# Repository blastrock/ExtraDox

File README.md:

# ExtraDox (v2)

The ExtraDox is a split keyboard based off the ErgoDox. The main difference is
that it has an additional row of keys on the top. Also, it is a low-profile
keyboard designed for Choc v1 switches.

It features:

- An additional row of keys over the ErgoDox
- An USB-C port
- A single-board design (actually two boards), no extra controller board
- A TRRS connection between the two sides
- The 3 usual status LED
- The case is only 8mm thick, the keys are 18mm high from the desk

## What you need to build this keyboard

- The PCBs and their components (the MCU is soldered on the main board)
- The 3D-printed case
- 14x M2.5x8 screws and nuts
- 10x rubber pads to put under the keyboard to prevent slipping
- 90x Kailh Choc Hotswap sockets
- 90x Kailh Choc switches
- 82x 1u key caps
- 4x 1.5u key caps
- 4x 2u key caps
- 3x SMD status LED (see the Kicad project for details)
- 2x TRRS connector (see the Kicad project for details)
- 1x TRRS cable
- 1x USB-c cable

## About this keyboard

### PCB

The PCB is designed in Kicad. It is a SMD design and the project includes
component references from JLCPCB.

### Case

The case is designed to be 3D-printed. The case is screwed together with 7
M2.5x8 screws on each side, and their corresponding bolts.

### Firmware

[Here](https://github.com/blastrock/qmk_firmware/tree/extradox/keyboards/extradox) is a a fork of the QMK firmware with support for the ExtraDox.

## Known issues

Some capacitors are located right under an hotswap socket. It is still possible
to solder it, but the socket gets a little tilted.

## License

This work is licensed under a [Creative Commons Attribution-NonCommercial-ShareAlike 4.0 International License](http://creativecommons.org/licenses/by-nc-sa/4.0/).

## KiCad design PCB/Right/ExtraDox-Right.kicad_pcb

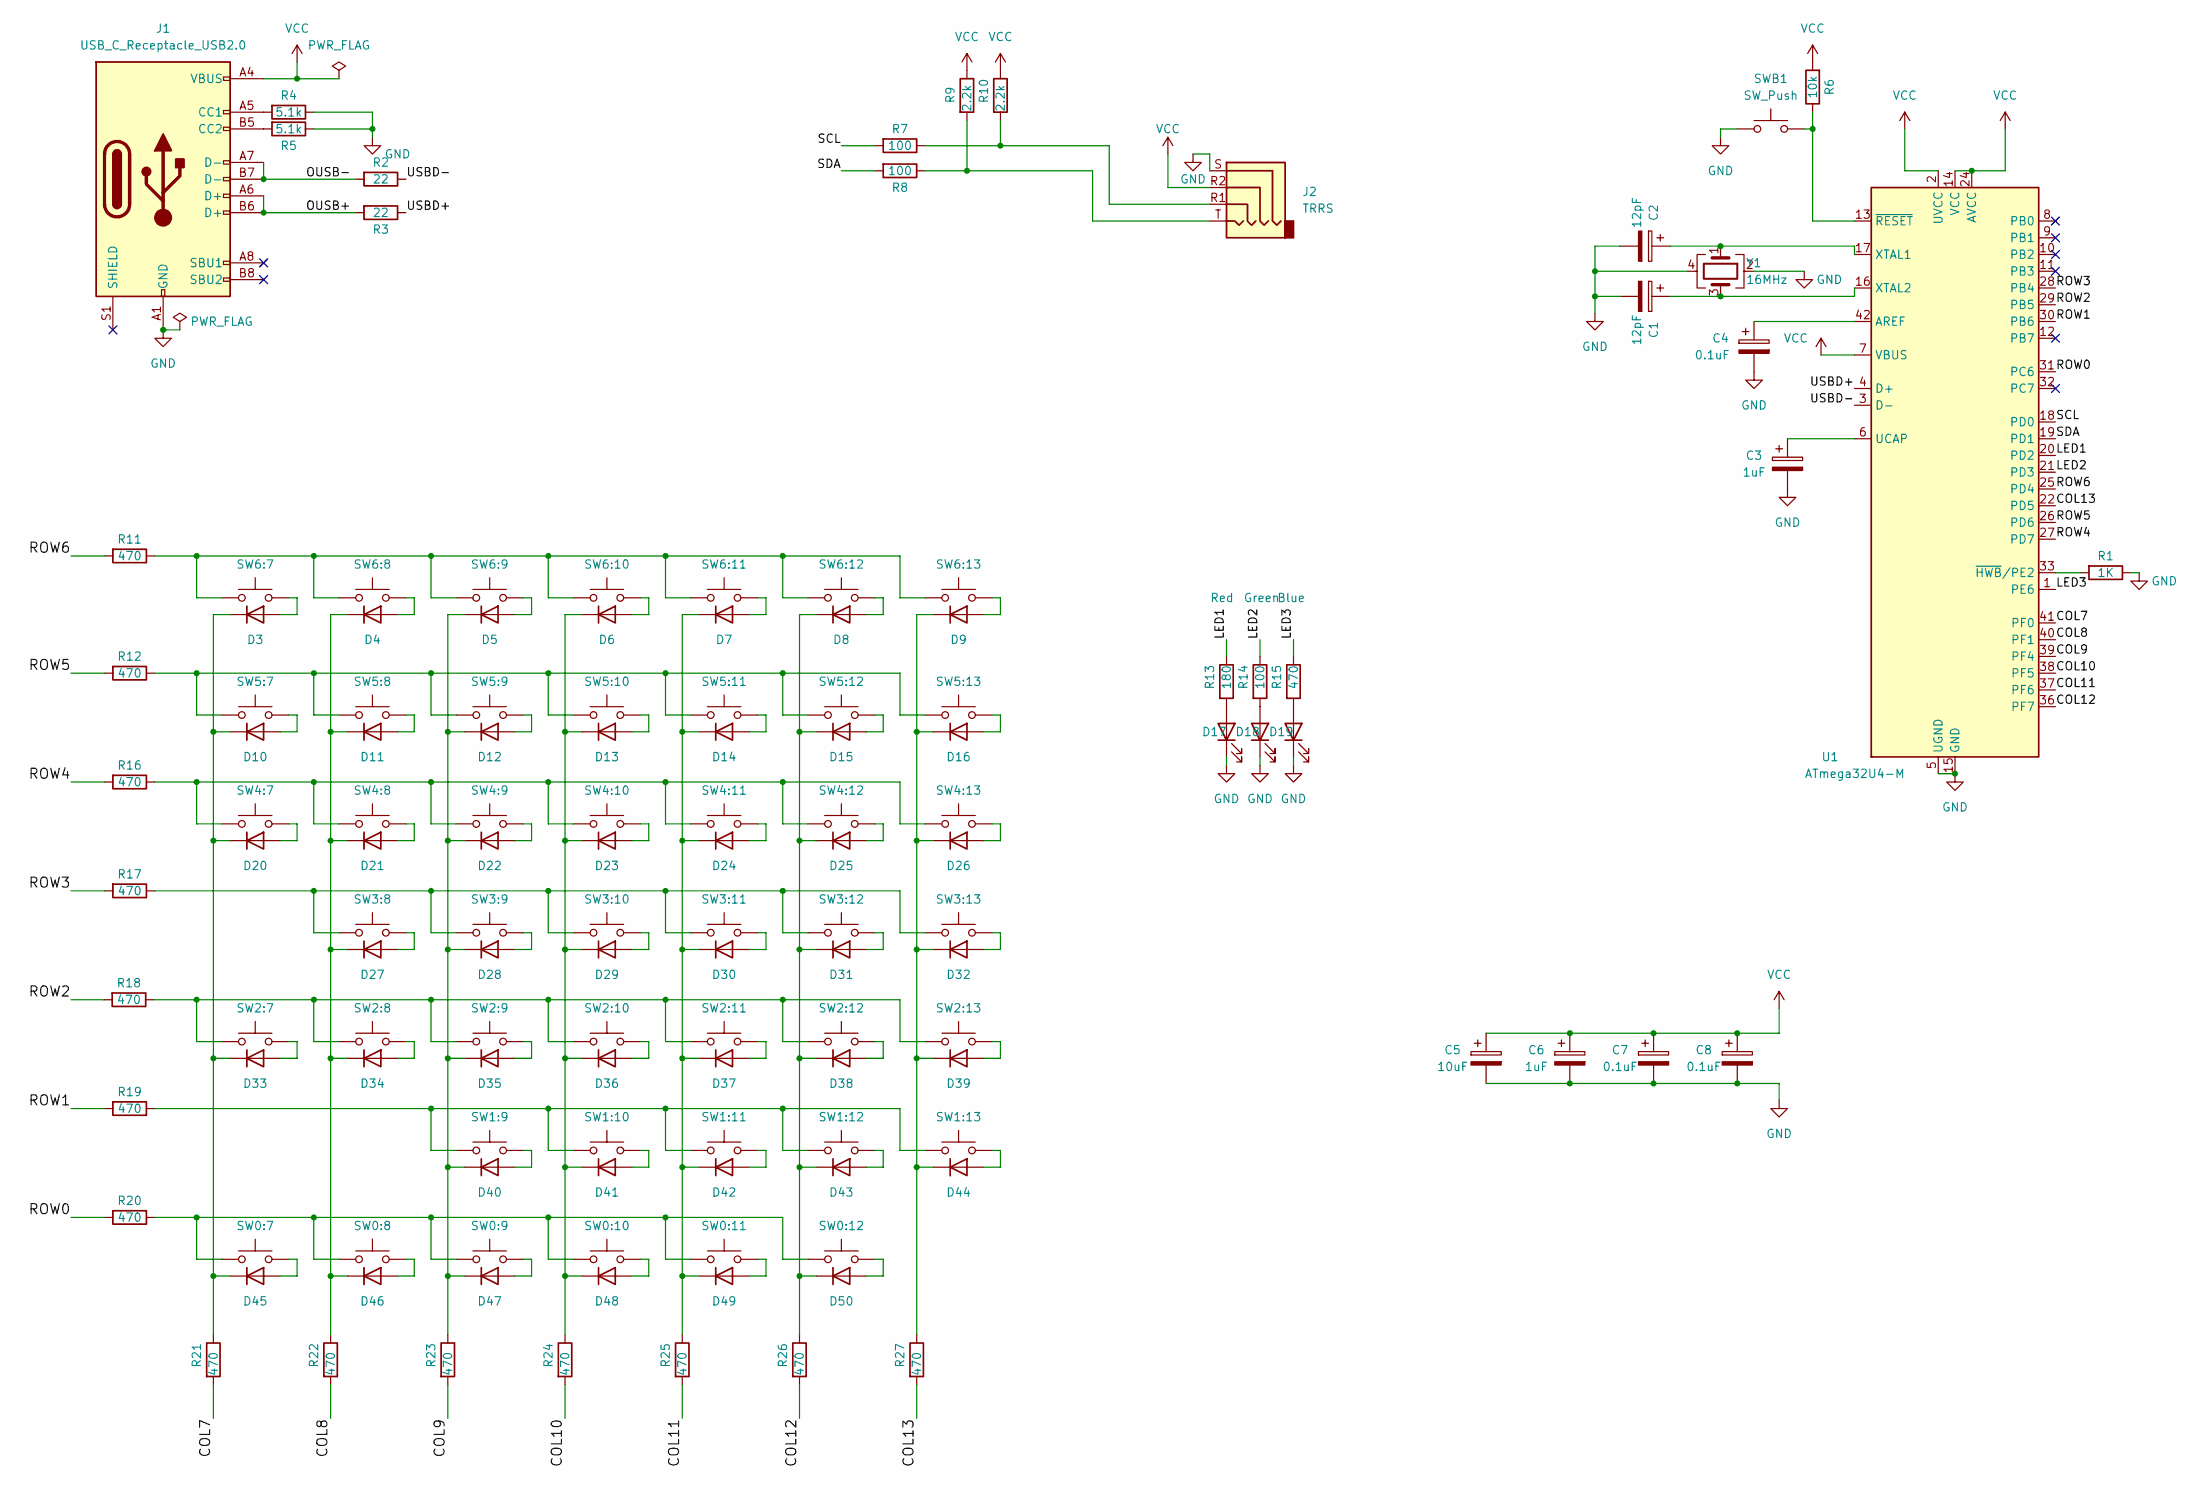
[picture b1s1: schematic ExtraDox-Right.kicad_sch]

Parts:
C1, C2: 12pF; C_0402_1005Metric; LCSC C1547
C3, C6: 1uF; C_0402_1005Metric; LCSC C52923
C4, C7, C8: 0.1uF; C_0402_1005Metric; LCSC C307331
C5: 10uF; C_0402_1005Metric; LCSC C15525
D3, D4, D5, D6, D7, D8, D9, D10, D11, D12, D13, D14, D15, D16, D20, D21, D22, D23, D24, D25, D26, D27, D28, D29, D30, D31, D32, D33, D34, D35, D36, D37, D38, D39, D40, D41, D42, D43, D44, D45, D46, D47, D48, D49, D50: D; D_SOD-123F; LCSC C64898
D17: Red; D_0603_1608Metric; LCSC C2286
D18: Green; D_0603_1608Metric; LCSC C72043
D19: Blue; D_0603_1608Metric; LCSC C72041
J1: USB_C_Receptacle_USB2.0; HRS_CX90M-16P; LCSC C2889324
J2: TRRS; TRRS-PJ-320A
R1: 1K; R_0402_1005Metric; LCSC C11702
R2, R3: 22; R_0402_1005Metric; LCSC C25092
R4, R5: 5.1k; R_0402_1005Metric; LCSC C25905
R6: 10k; R_0402_1005Metric; LCSC C25744
R7, R8, R14: 100; R_0402_1005Metric; LCSC C25076
R9, R10: 2.2k; R_0402_1005Metric; LCSC C25879
R11, R12, R15, R16, R17, R18, R19, R20, R21, R22, R23, R24, R25, R26, R27: 470; R_0402_1005Metric; LCSC C25117
R13: 180; R_0402_1005Metric; LCSC C25082
SW0:7, SW0:8, SW0:9, SW0:12, SW1:9, SW1:10, SW1:11, SW1:12, SW1:13, SW2:8, SW2:9, SW2:10, SW2:11, SW2:12, SW2:13, SW3:8, SW3:9, SW3:10, SW3:11, SW3:12, SW3:13, SW4:8, SW4:9, SW4:10, SW4:11, SW4:12, SW4:13, SW5:7, SW5:8, SW5:9, SW5:10, SW5:11, SW5:12, SW5:13, SW6:7, SW6:8, SW6:9, SW6:10, SW6:11, SW6:12, SW6:13: SW_Push; KailhHotswapChoc1
SW0:10, SW0:11: SW_Push; KailhHotswapChoc2
SW2:7, SW4:7: SW_Push; KailhHotswapChoc15
SWB1: SW_Push; TS-1087S; LCSC C455263
U1: ATmega32U4-M; QFN-44-1EP_7x7mm_P0.5mm_EP5.2x5.2mm_ThermalVias_JLCPCB; LCSC C112161
Y1: 16MHz; Crystal_SMD_3225-4Pin_3.2x2.5mm; LCSC C13738

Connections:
/COL7: R21.2, U1.41 (PF0)
/COL8: R22.2, U1.40 (PF1)
/COL9: R23.2, U1.39 (PF4)
/COL10: R24.2, U1.38 (PF5)
/COL11: R25.2, U1.37 (PF6)
/COL12: R26.2, U1.36 (PF7)
/COL13: R27.2, U1.22 (PD5)
/LED1: R13.1, U1.20 (PD2)
/LED2: R14.1, U1.21 (PD3)
/LED3: R15.1, U1.1 (PE6)
/OUSB+: J1.A6 (D+), J1.B6 (D+), R3.2
/OUSB-: J1.A7 (D-), J1.B7 (D-), R2.2
/ROW0: R20.2, U1.31 (PC6)
/ROW1: R19.2, U1.30 (PB6)
/ROW2: R18.2, U1.29 (PB5)
/ROW3: R17.2, U1.28 (PB4)
/ROW4: R16.2, U1.27 (PD7)
/ROW5: R12.2, U1.26 (PD6)
/ROW6: R11.2, U1.25 (PD4)
/SCL: R7.2, U1.18 (PD0)
/SDA: R8.2, U1.19 (PD1)
/USBD+: R3.1, U1.4 (D+)
/USBD-: R2.1, U1.3 (D-)
GND: C1.2, C2.2, C3.2, C4.2, C5.2, C6.2, C7.2, C8.2, D17.1 (K), D18.1 (K), D19.1 (K), J1.A1 (GND), J1.A12 (GND), J1.B1 (GND), J1.B12 (GND), J2.S, R1.1, R4.1, R5.1, SWB1.1, U1.5 (UGND), U1.15 (GND), U1.23 (GND), U1.35 (GND), U1.43 (GND), U1.45 (GND), Y1.2, Y1.4
unnamed: C1.1, U1.16 (XTAL2), Y1.3
unnamed: C2.1, U1.17 (XTAL1), Y1.1
unnamed: C3.1, U1.6 (UCAP)
unnamed: C4.1, U1.42 (AREF)
unnamed: D3.2 (A), SW6:7.2
unnamed: D4.2 (A), SW6:8.2
unnamed: D5.2 (A), SW6:9.2
unnamed: D6.2 (A), SW6:10.2
unnamed: D7.2 (A), SW6:11.2
unnamed: D8.2 (A), SW6:12.2
unnamed: D9.2 (A), SW6:13.2
unnamed: D3.1 (K), D10.1 (K), D20.1 (K), D33.1 (K), D45.1 (K), R21.1
unnamed: D10.2 (A), SW5:7.2
unnamed: D4.1 (K), D11.1 (K), D21.1 (K), D27.1 (K), D34.1 (K), D46.1 (K), R22.1
unnamed: D11.2 (A), SW5:8.2
unnamed: D5.1 (K), D12.1 (K), D22.1 (K), D28.1 (K), D35.1 (K), D40.1 (K), D47.1 (K), R23.1
unnamed: D12.2 (A), SW5:9.2
unnamed: D6.1 (K), D13.1 (K), D23.1 (K), D29.1 (K), D36.1 (K), D41.1 (K), D48.1 (K), R24.1
unnamed: D13.2 (A), SW5:10.2
unnamed: D7.1 (K), D14.1 (K), D24.1 (K), D30.1 (K), D37.1 (K), D42.1 (K), D49.1 (K), R25.1
unnamed: D14.2 (A), SW5:11.2
unnamed: D8.1 (K), D15.1 (K), D25.1 (K), D31.1 (K), D38.1 (K), D43.1 (K), D50.1 (K), R26.1
unnamed: D15.2 (A), SW5:12.2
unnamed: D9.1 (K), D16.1 (K), D26.1 (K), D32.1 (K), D39.1 (K), D44.1 (K), R27.1
unnamed: D16.2 (A), SW5:13.2
unnamed: D17.2 (A), R13.2
unnamed: D18.2 (A), R14.2
unnamed: D19.2 (A), R15.2
unnamed: D20.2 (A), SW4:7.2
unnamed: D21.2 (A), SW4:8.2
unnamed: D22.2 (A), SW4:9.2
unnamed: D23.2 (A), SW4:10.2
unnamed: D24.2 (A), SW4:11.2
unnamed: D25.2 (A), SW4:12.2
unnamed: D26.2 (A), SW4:13.2
unnamed: D27.2 (A), SW3:8.2
unnamed: D28.2 (A), SW3:9.2
unnamed: D29.2 (A), SW3:10.2
unnamed: D30.2 (A), SW3:11.2
unnamed: D31.2 (A), SW3:12.2
unnamed: D32.2 (A), SW3:13.2
unnamed: D33.2 (A), SW2:7.2
unnamed: D34.2 (A), SW2:8.2
unnamed: D35.2 (A), SW2:9.2
unnamed: D36.2 (A), SW2:10.2
unnamed: D37.2 (A), SW2:11.2
unnamed: D38.2 (A), SW2:12.2
unnamed: D39.2 (A), SW2:13.2
unnamed: D40.2 (A), SW1:9.2
unnamed: D41.2 (A), SW1:10.2
unnamed: D42.2 (A), SW1:11.2
unnamed: D43.2 (A), SW1:12.2
unnamed: D44.2 (A), SW1:13.2
unnamed: D45.2 (A), SW0:7.2
unnamed: D46.2 (A), SW0:8.2
unnamed: D47.2 (A), SW0:9.2
unnamed: D48.2 (A), SW0:10.2
unnamed: D49.2 (A), SW0:11.2
unnamed: D50.2 (A), SW0:12.2
unnamed: J1.A5 (CC1), R4.2
unnamed: J1.B5 (CC2), R5.2
unnamed: J2.R1, R7.1, R10.2
unnamed: J2.T, R8.1, R9.2
unnamed: R1.2, U1.33 (~HWB/PE2)
unnamed: R6.1, SWB1.2, U1.13 (~RESET)
unnamed: R11.1, SW6:7.1, SW6:8.1, SW6:9.1, SW6:10.1, SW6:11.1, SW6:12.1, SW6:13.1
unnamed: R12.1, SW5:7.1, SW5:8.1, SW5:9.1, SW5:10.1, SW5:11.1, SW5:12.1, SW5:13.1
unnamed: R16.1, SW4:7.1, SW4:8.1, SW4:9.1, SW4:10.1, SW4:11.1, SW4:12.1, SW4:13.1
unnamed: R17.1, SW3:8.1, SW3:9.1, SW3:10.1, SW3:11.1, SW3:12.1, SW3:13.1
unnamed: R18.1, SW2:7.1, SW2:8.1, SW2:9.1, SW2:10.1, SW2:11.1, SW2:12.1, SW2:13.1
unnamed: R19.1, SW1:9.1, SW1:10.1, SW1:11.1, SW1:12.1, SW1:13.1
unnamed: R20.1, SW0:7.1, SW0:8.1, SW0:9.1, SW0:10.1, SW0:11.1, SW0:12.1
VCC: C5.1, C6.1, C7.1, C8.1, J1.A4 (VBUS), J1.A9 (VBUS), J1.B4 (VBUS), J1.B9 (VBUS), J2.R2, R6.2, R9.1, R10.1, U1.2 (UVCC), U1.7 (VBUS), U1.14 (VCC), U1.24 (AVCC), U1.34 (VCC), U1.44 (AVCC)

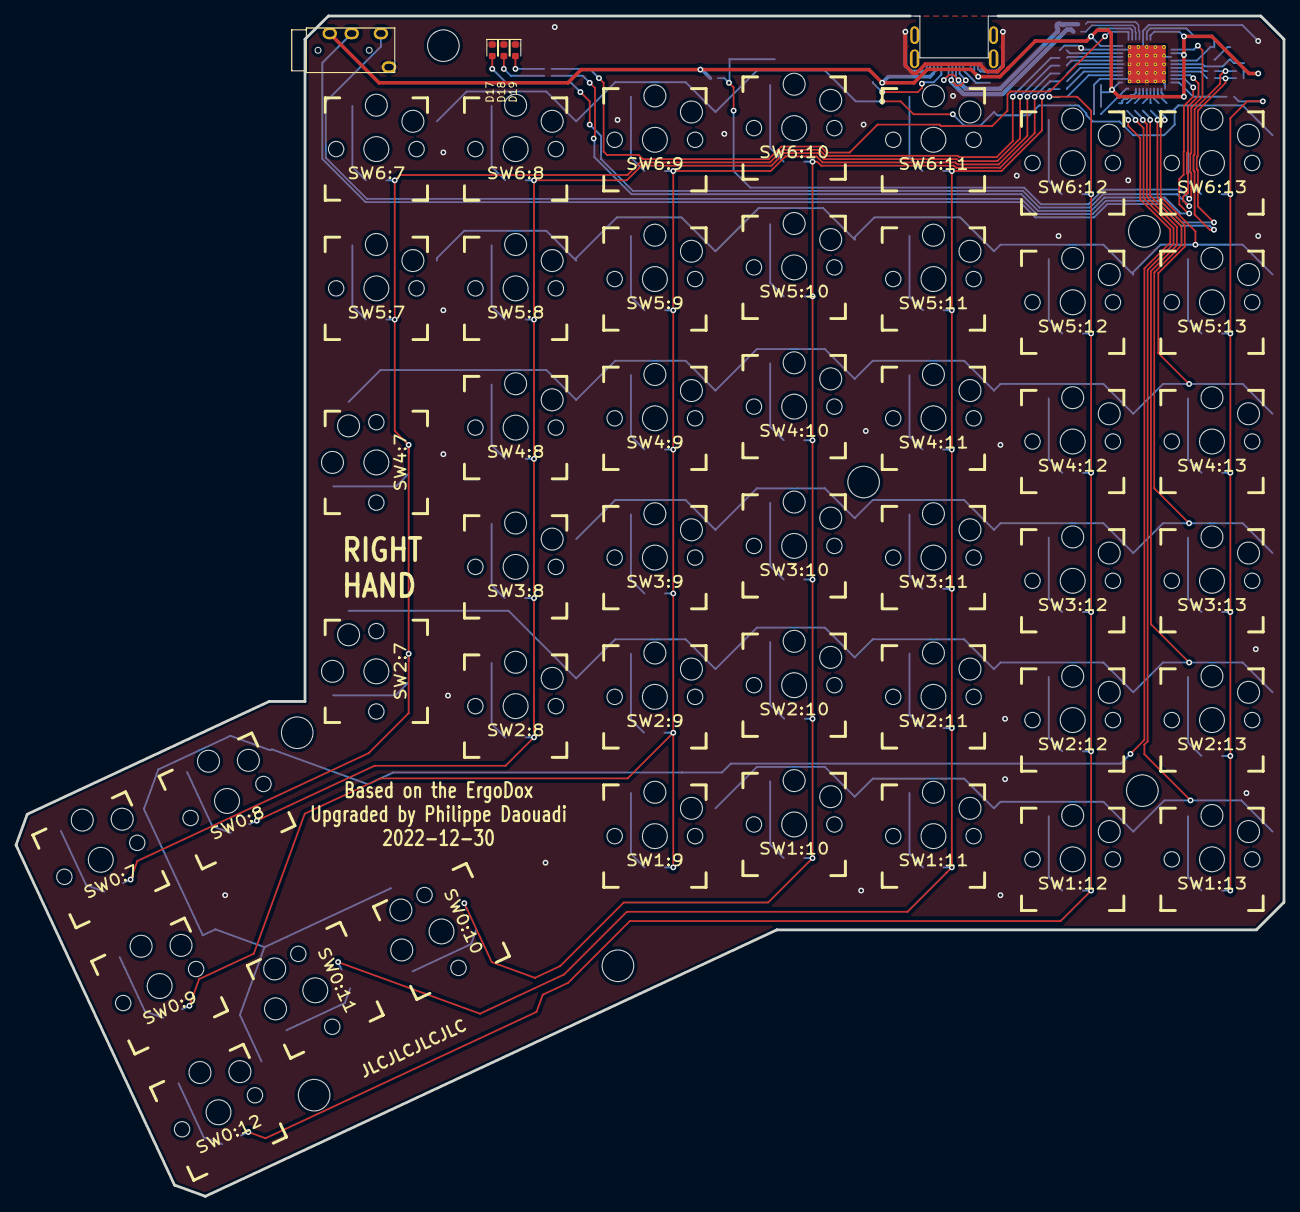
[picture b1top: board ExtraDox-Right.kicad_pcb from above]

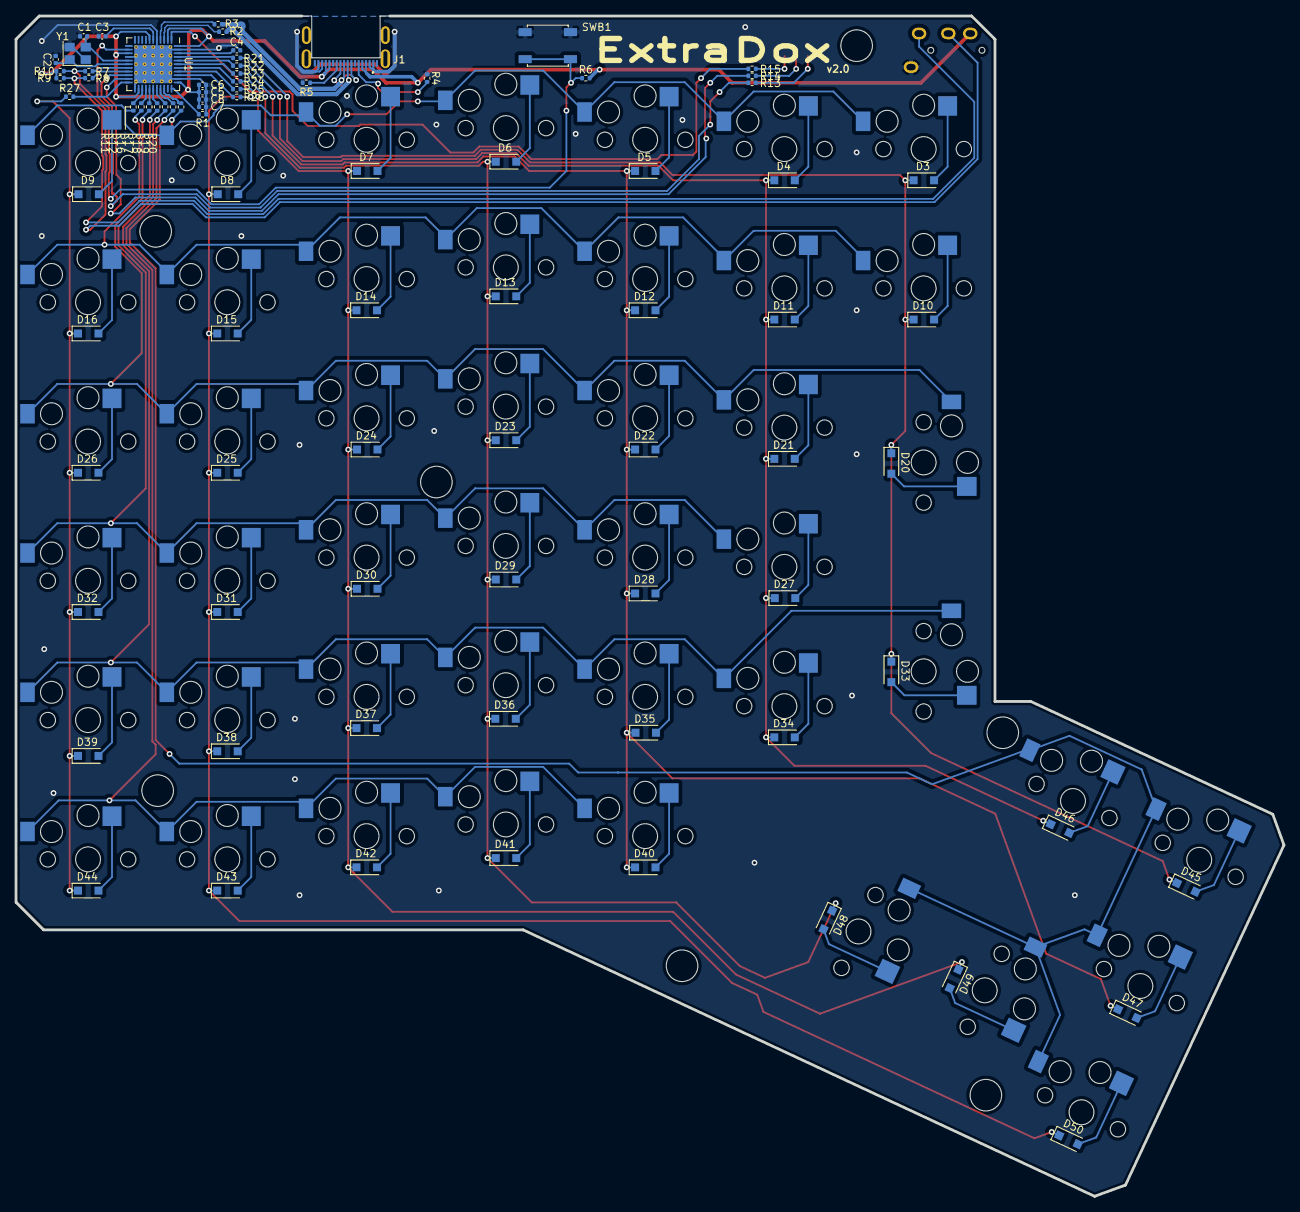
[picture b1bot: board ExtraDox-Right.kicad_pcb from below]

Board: 2 copper layers, 173.4 x 161.4 mm, 133 parts (84 on the bottom side), 97 nets.

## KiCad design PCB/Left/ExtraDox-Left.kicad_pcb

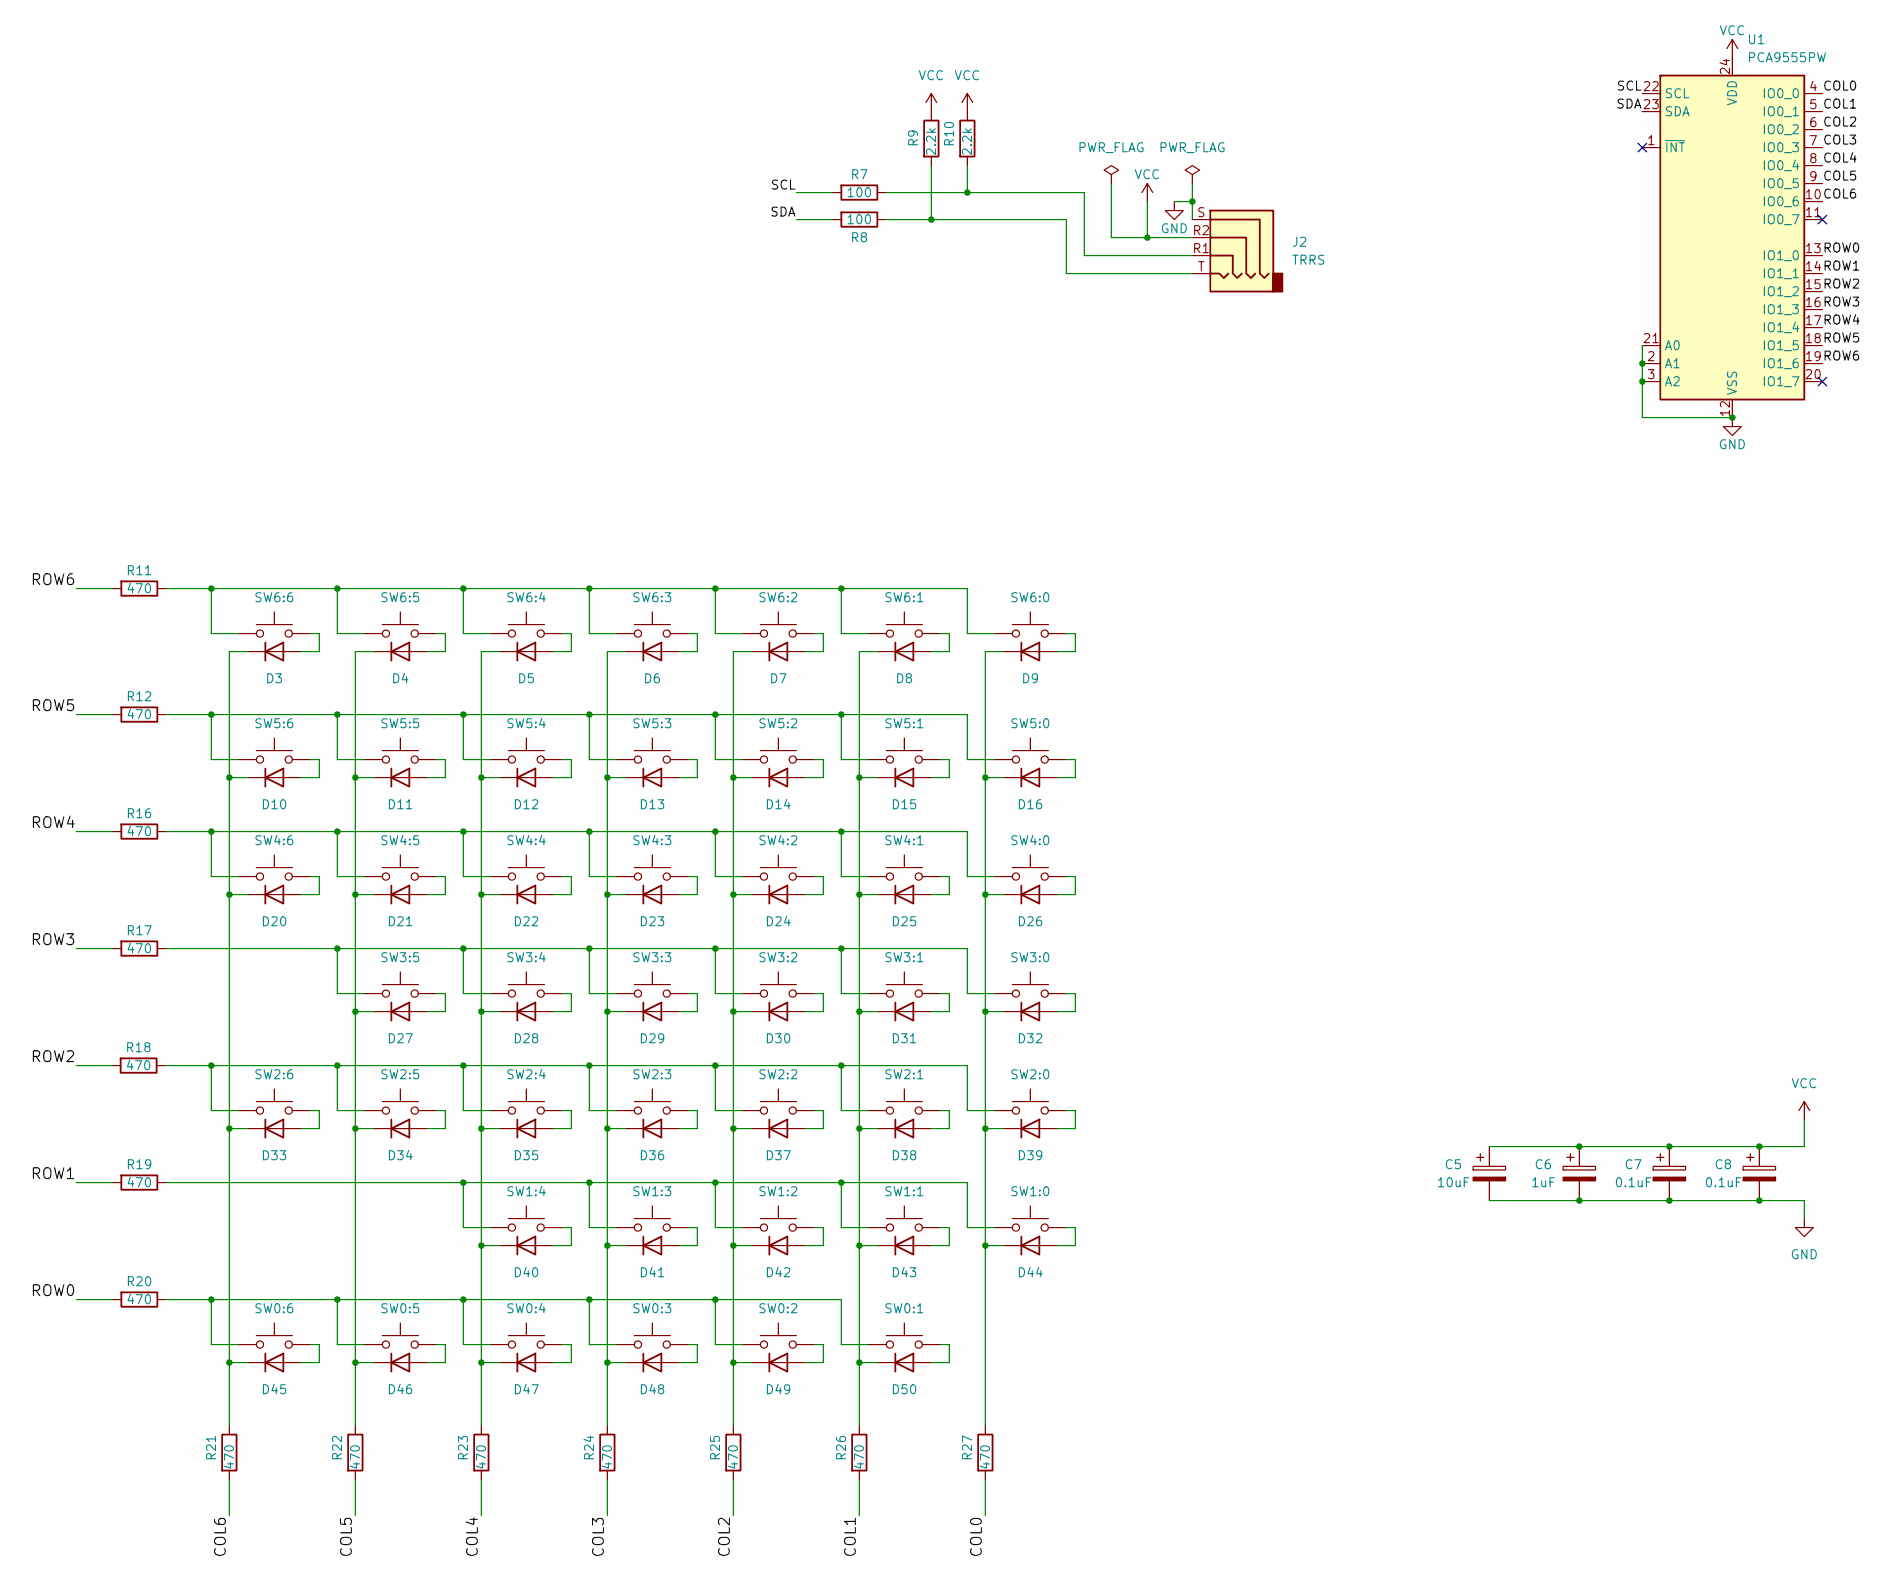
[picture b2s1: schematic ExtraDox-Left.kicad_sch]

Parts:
C5: 10uF; C_0402_1005Metric; LCSC C15525
C6: 1uF; C_0402_1005Metric; LCSC C52923
C7, C8: 0.1uF; C_0402_1005Metric; LCSC C307331
D3, D4, D5, D6, D7, D8, D9, D10, D11, D12, D13, D14, D15, D16, D20, D21, D22, D23, D24, D25, D26, D27, D28, D29, D30, D31, D32, D33, D34, D35, D36, D37, D38, D39, D40, D41, D42, D43, D44, D45, D46, D47, D48, D49, D50: D; D_SOD-123F; LCSC C64898
J2: TRRS; TRRS-PJ-320A
R7, R8: 100; R_0402_1005Metric; LCSC C25076
R9, R10: 2.2k; R_0402_1005Metric; LCSC C25879
R11, R12, R16, R17, R18, R19, R20, R21, R22, R23, R24, R25, R26, R27: 470; R_0402_1005Metric; LCSC C25117
SW0:1, SW0:4, SW0:5, SW0:6, SW1:0, SW1:1, SW1:2, SW1:3, SW1:4, SW2:0, SW2:1, SW2:2, SW2:3, SW2:4, SW2:5, SW3:0, SW3:1, SW3:2, SW3:3, SW3:4, SW3:5, SW4:0, SW4:1, SW4:2, SW4:3, SW4:4, SW4:5, SW5:0, SW5:1, SW5:2, SW5:3, SW5:4, SW5:5, SW5:6, SW6:0, SW6:1, SW6:2, SW6:3, SW6:4, SW6:5, SW6:6: SW_Push; KailhHotswapChoc1
SW0:2, SW0:3: SW_Push; KailhHotswapChoc2
SW2:6, SW4:6: SW_Push; KailhHotswapChoc15
U1: PCA9555PW; TSSOP-24_4.4x7.8mm_P0.65mm_JLCPCB; LCSC C128392

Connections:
/COL0: R27.2, U1.4 (IO0_0)
/COL1: R26.2, U1.5 (IO0_1)
/COL2: R25.2, U1.6 (IO0_2)
/COL3: R24.2, U1.7 (IO0_3)
/COL4: R23.2, U1.8 (IO0_4)
/COL5: R22.2, U1.9 (IO0_5)
/COL6: R21.2, U1.10 (IO0_6)
/ROW0: R20.2, U1.13 (IO1_0)
/ROW1: R19.2, U1.14 (IO1_1)
/ROW2: R18.2, U1.15 (IO1_2)
/ROW3: R17.2, U1.16 (IO1_3)
/ROW4: R16.2, U1.17 (IO1_4)
/ROW5: R12.2, U1.18 (IO1_5)
/ROW6: R11.2, U1.19 (IO1_6)
/SCL: R7.2, U1.22 (SCL)
/SDA: R8.2, U1.23 (SDA)
GND: C5.2, C6.2, C7.2, C8.2, J2.S, U1.2 (A1), U1.3 (A2), U1.12 (VSS), U1.21 (A0)
unnamed: D3.2 (A), SW6:6.2
unnamed: D4.2 (A), SW6:5.2
unnamed: D5.2 (A), SW6:4.2
unnamed: D6.2 (A), SW6:3.2
unnamed: D7.2 (A), SW6:2.2
unnamed: D8.2 (A), SW6:1.2
unnamed: D9.2 (A), SW6:0.2
unnamed: D3.1 (K), D10.1 (K), D20.1 (K), D33.1 (K), D45.1 (K), R21.1
unnamed: D10.2 (A), SW5:6.2
unnamed: D4.1 (K), D11.1 (K), D21.1 (K), D27.1 (K), D34.1 (K), D46.1 (K), R22.1
unnamed: D11.2 (A), SW5:5.2
unnamed: D5.1 (K), D12.1 (K), D22.1 (K), D28.1 (K), D35.1 (K), D40.1 (K), D47.1 (K), R23.1
unnamed: D12.2 (A), SW5:4.2
unnamed: D6.1 (K), D13.1 (K), D23.1 (K), D29.1 (K), D36.1 (K), D41.1 (K), D48.1 (K), R24.1
unnamed: D13.2 (A), SW5:3.2
unnamed: D7.1 (K), D14.1 (K), D24.1 (K), D30.1 (K), D37.1 (K), D42.1 (K), D49.1 (K), R25.1
unnamed: D14.2 (A), SW5:2.2
unnamed: D8.1 (K), D15.1 (K), D25.1 (K), D31.1 (K), D38.1 (K), D43.1 (K), D50.1 (K), R26.1
unnamed: D15.2 (A), SW5:1.2
unnamed: D9.1 (K), D16.1 (K), D26.1 (K), D32.1 (K), D39.1 (K), D44.1 (K), R27.1
unnamed: D16.2 (A), SW5:0.2
unnamed: D20.2 (A), SW4:6.2
unnamed: D21.2 (A), SW4:5.2
unnamed: D22.2 (A), SW4:4.2
unnamed: D23.2 (A), SW4:3.2
unnamed: D24.2 (A), SW4:2.2
unnamed: D25.2 (A), SW4:1.2
unnamed: D26.2 (A), SW4:0.2
unnamed: D27.2 (A), SW3:5.2
unnamed: D28.2 (A), SW3:4.2
unnamed: D29.2 (A), SW3:3.2
unnamed: D30.2 (A), SW3:2.2
unnamed: D31.2 (A), SW3:1.2
unnamed: D32.2 (A), SW3:0.2
unnamed: D33.2 (A), SW2:6.2
unnamed: D34.2 (A), SW2:5.2
unnamed: D35.2 (A), SW2:4.2
unnamed: D36.2 (A), SW2:3.2
unnamed: D37.2 (A), SW2:2.2
unnamed: D38.2 (A), SW2:1.2
unnamed: D39.2 (A), SW2:0.2
unnamed: D40.2 (A), SW1:4.2
unnamed: D41.2 (A), SW1:3.2
unnamed: D42.2 (A), SW1:2.2
unnamed: D43.2 (A), SW1:1.2
unnamed: D44.2 (A), SW1:0.2
unnamed: D45.2 (A), SW0:6.2
unnamed: D46.2 (A), SW0:5.2
unnamed: D47.2 (A), SW0:4.2
unnamed: D48.2 (A), SW0:3.2
unnamed: D49.2 (A), SW0:2.2
unnamed: D50.2 (A), SW0:1.2
unnamed: J2.R1, R7.1, R10.2
unnamed: J2.T, R8.1, R9.2
unnamed: R11.1, SW6:0.1, SW6:1.1, SW6:2.1, SW6:3.1, SW6:4.1, SW6:5.1, SW6:6.1
unnamed: R12.1, SW5:0.1, SW5:1.1, SW5:2.1, SW5:3.1, SW5:4.1, SW5:5.1, SW5:6.1
unnamed: R16.1, SW4:0.1, SW4:1.1, SW4:2.1, SW4:3.1, SW4:4.1, SW4:5.1, SW4:6.1
unnamed: R17.1, SW3:0.1, SW3:1.1, SW3:2.1, SW3:3.1, SW3:4.1, SW3:5.1
unnamed: R18.1, SW2:0.1, SW2:1.1, SW2:2.1, SW2:3.1, SW2:4.1, SW2:5.1, SW2:6.1
unnamed: R19.1, SW1:0.1, SW1:1.1, SW1:2.1, SW1:3.1, SW1:4.1
unnamed: R20.1, SW0:1.1, SW0:2.1, SW0:3.1, SW0:4.1, SW0:5.1, SW0:6.1
VCC: C5.1, C6.1, C7.1, C8.1, J2.R2, R9.1, R10.1, U1.24 (VDD)

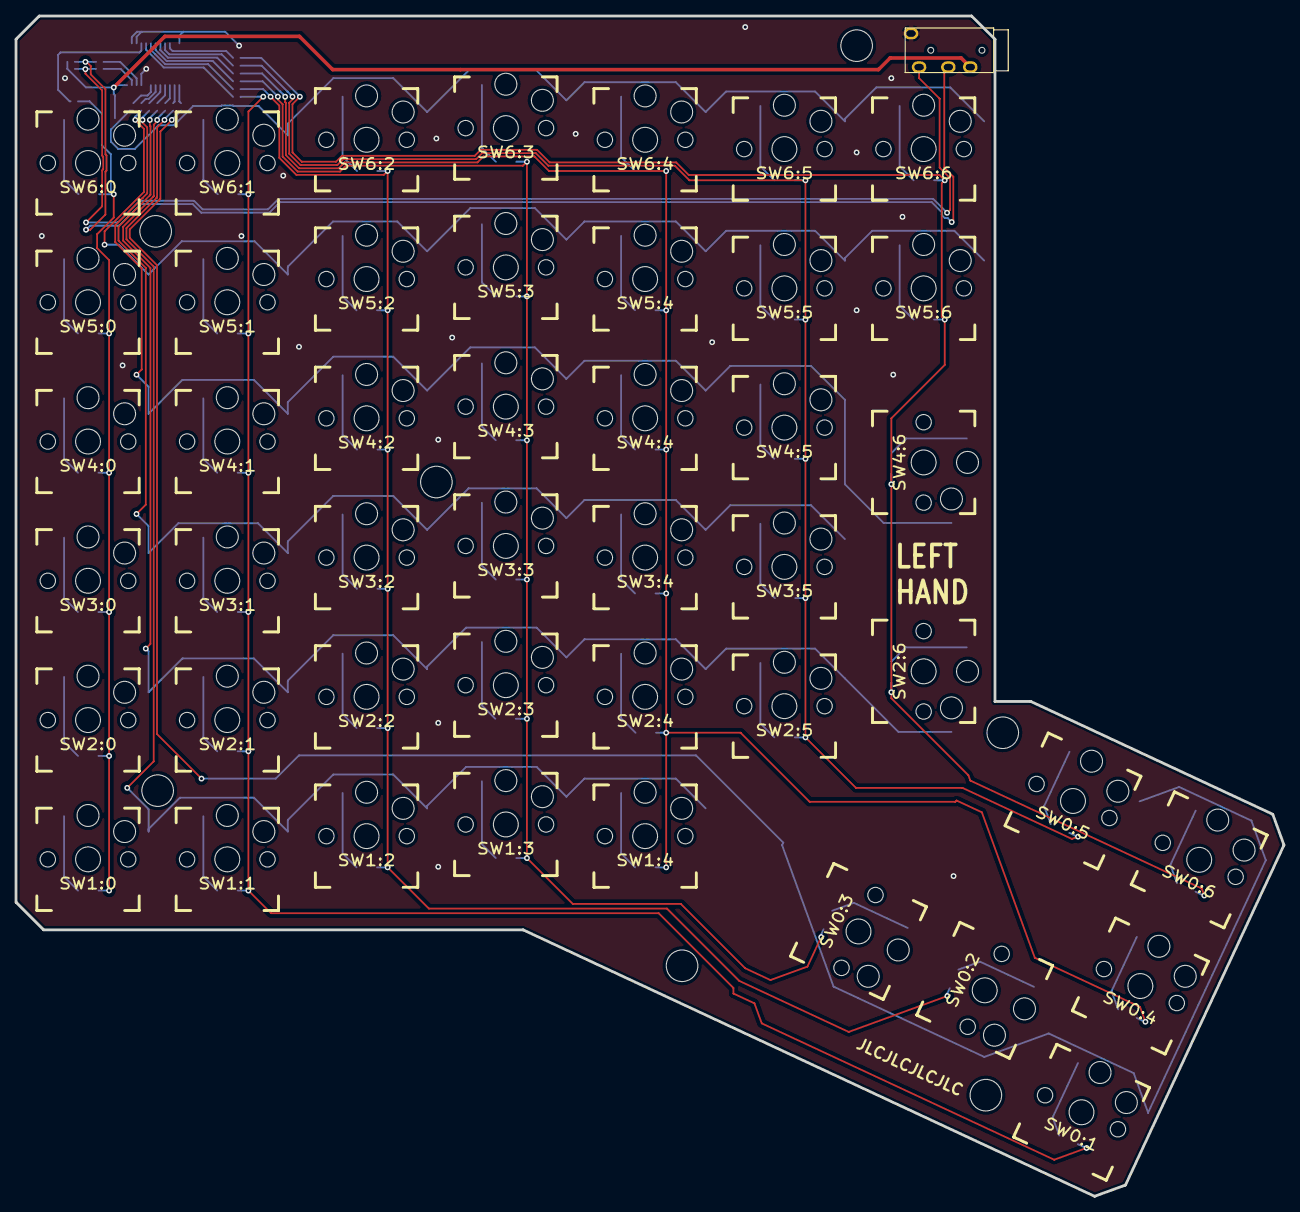
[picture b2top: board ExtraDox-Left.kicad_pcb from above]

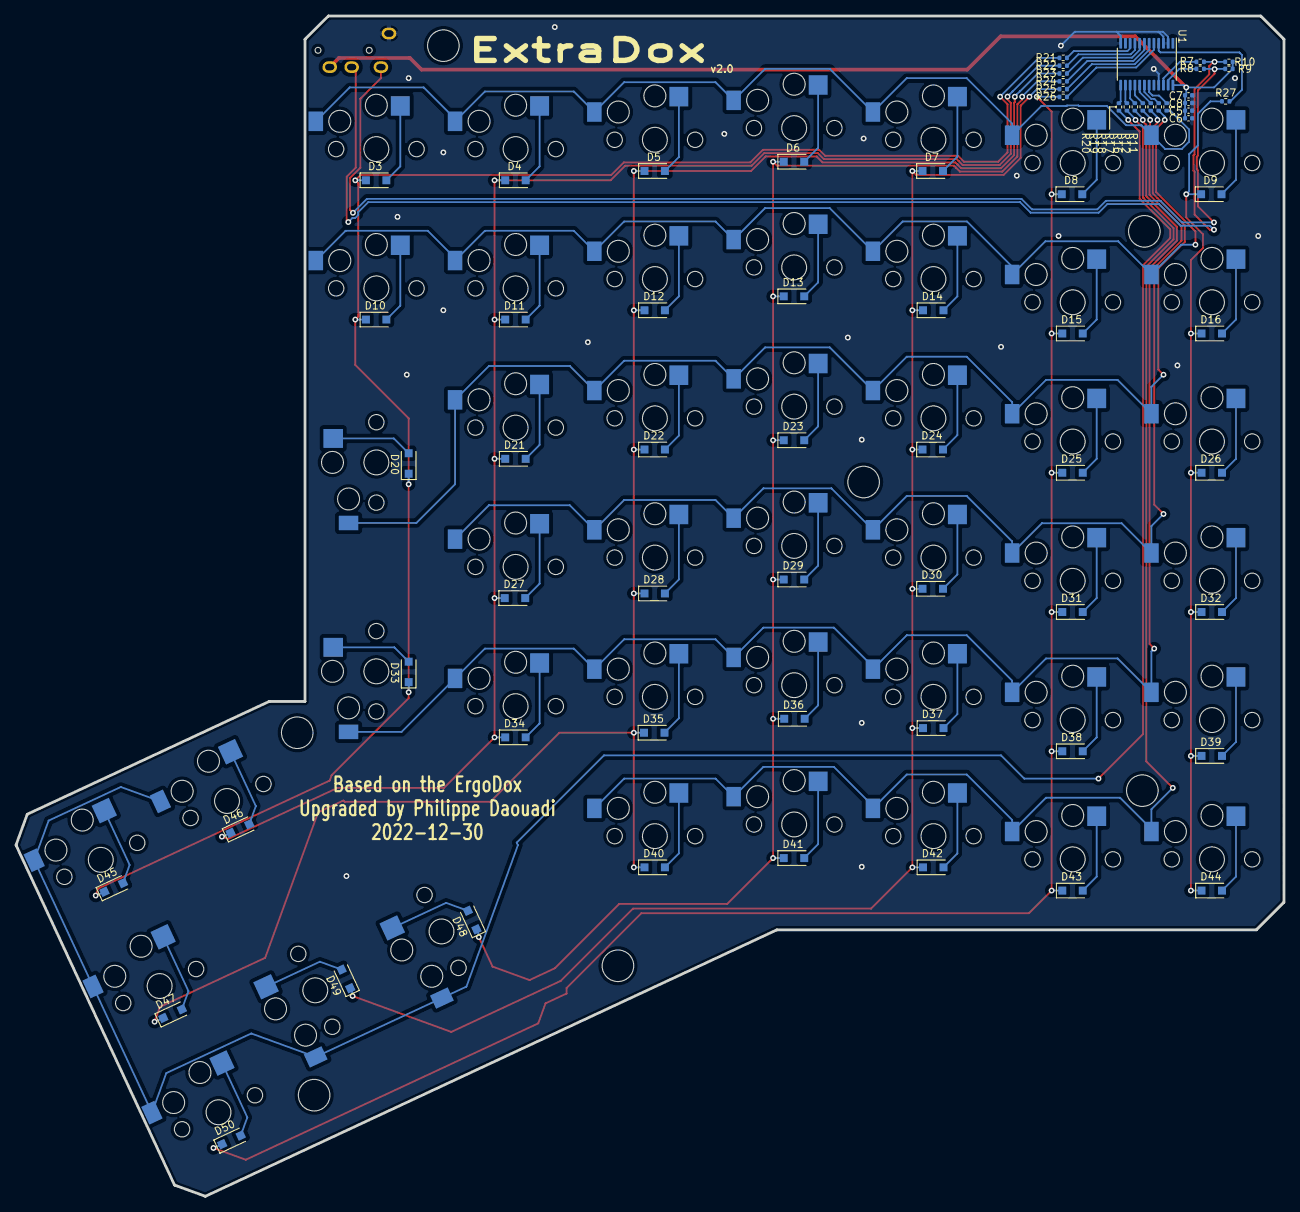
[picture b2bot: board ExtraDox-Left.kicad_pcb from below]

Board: 2 copper layers, 173.4 x 161.4 mm, 114 parts (68 on the bottom side), 79 nets.

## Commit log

2023-05-06 README: add firmware
2023-05-06 Add license
2023-05-13 README: add note about buying boards
2023-05-29 README: fix choc version
2024-11-03 README: no more boards to sell
